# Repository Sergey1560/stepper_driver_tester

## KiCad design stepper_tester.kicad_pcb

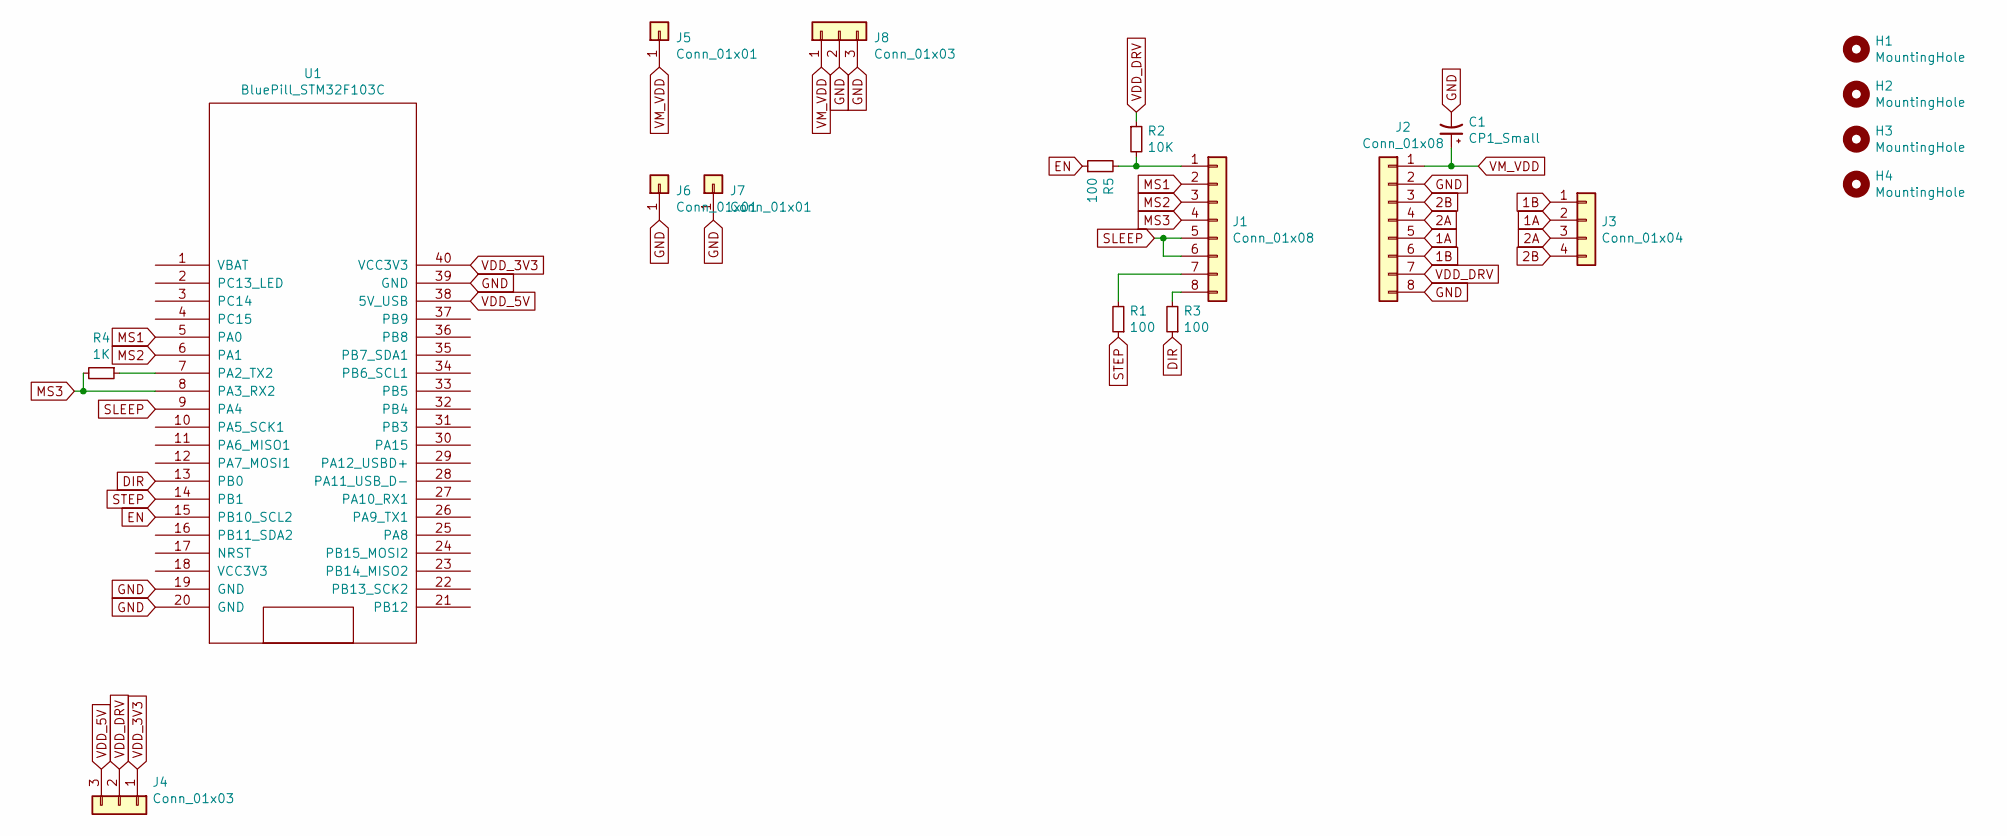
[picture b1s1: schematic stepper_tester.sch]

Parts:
C1: CP1_Small; CP_Radial_D8.0mm_P5.00mm
H1, H2, H3, H4: MountingHole; MountingHole_3.2mm_M3
J1, J2: Conn_01x08; PinSocket_1x08_P2.54mm_Vertical
J3: Conn_01x04; JST_XH_B4B-XH-A_1x04_P2.50mm_Vertical
J4: Conn_01x03; PinHeader_1x03_P2.54mm_Vertical
J5, J6, J7: Conn_01x01; PinHeader_1x01_P2.54mm_Vertical
J8: Conn_01x03; DC55x21THT
R1, R3, R5: 100; R_0805_2012Metric_Pad1.15x1.40mm_HandSolder
R2: 10K; R_0805_2012Metric_Pad1.15x1.40mm_HandSolder
R4: 1K; R_0805_2012Metric_Pad1.15x1.40mm_HandSolder
U1: BluePill_STM32F103C; ChinaBluePill

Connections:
1A: J2.5, J3.2
1B: J2.6, J3.1
2A: J2.4, J3.3
2B: J2.3, J3.4
DIR: R3.1, U1.13 (PB0)
EN: R5.1, U1.15 (PB10_SCL2)
GND: C1.2, J2.2, J2.8, J6.1, J7.1, J8.2, J8.3, U1.19 (GND), U1.20 (GND), U1.39 (GND)
MS1: J1.2, U1.5 (PA0)
MS2: J1.3, U1.6 (PA1)
MS3: J1.4, R4.2, U1.8 (PA3_RX2)
unnamed: J1.1, R2.2, R5.2
unnamed: J1.7, R1.2
unnamed: J1.8, R3.2
unnamed: R4.1, U1.7 (PA2_TX2)
SLEEP: J1.5, J1.6, U1.9 (PA4)
STEP: R1.1, U1.14 (PB1)
VDD_3V3: J4.1, U1.40 (VCC3V3)
VDD_5V: J4.3, U1.38 (5V_USB)
VDD_DRV: J2.7, J4.2, R2.1
VM_VDD: C1.1, J2.1, J5.1, J8.1

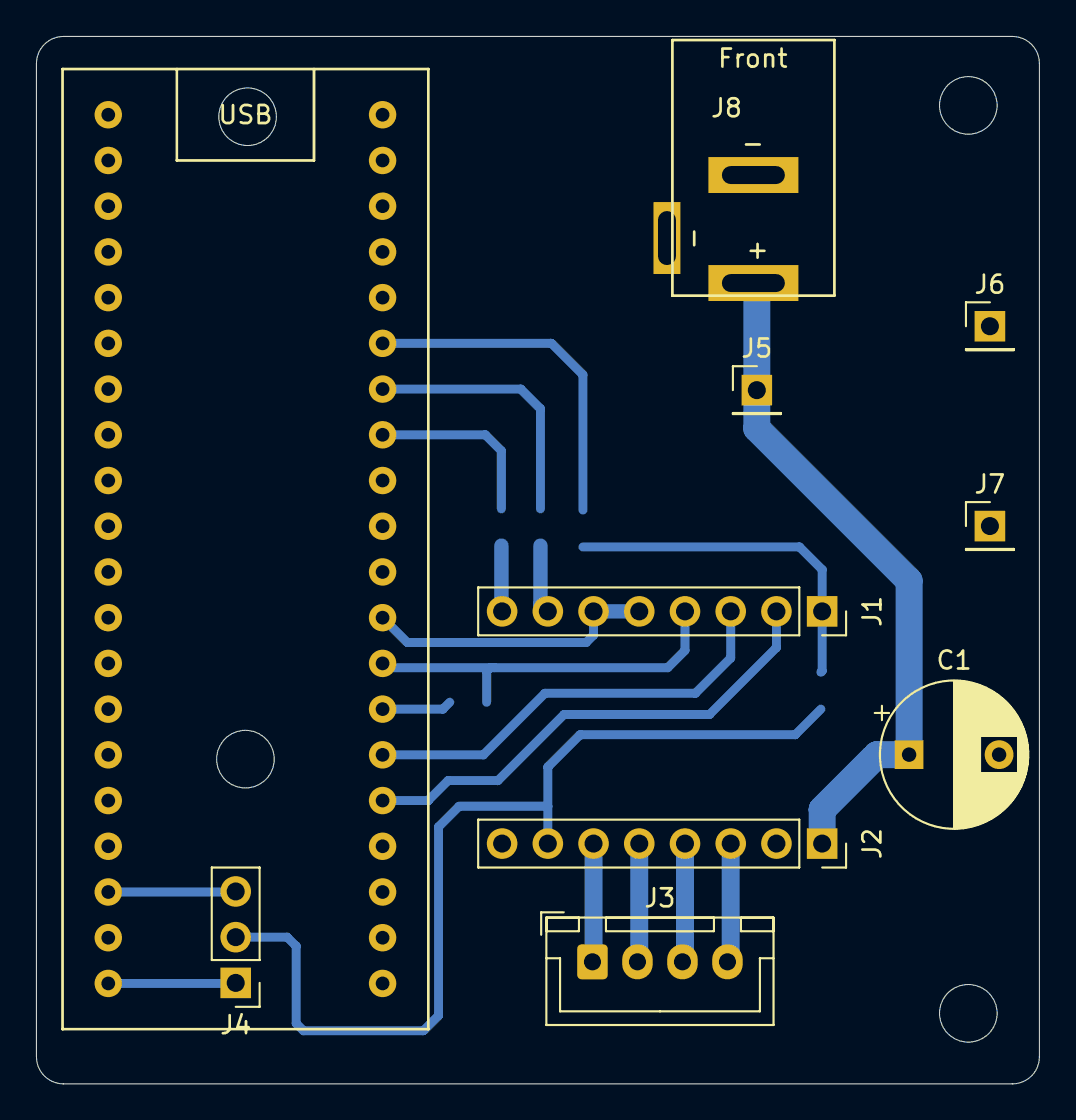
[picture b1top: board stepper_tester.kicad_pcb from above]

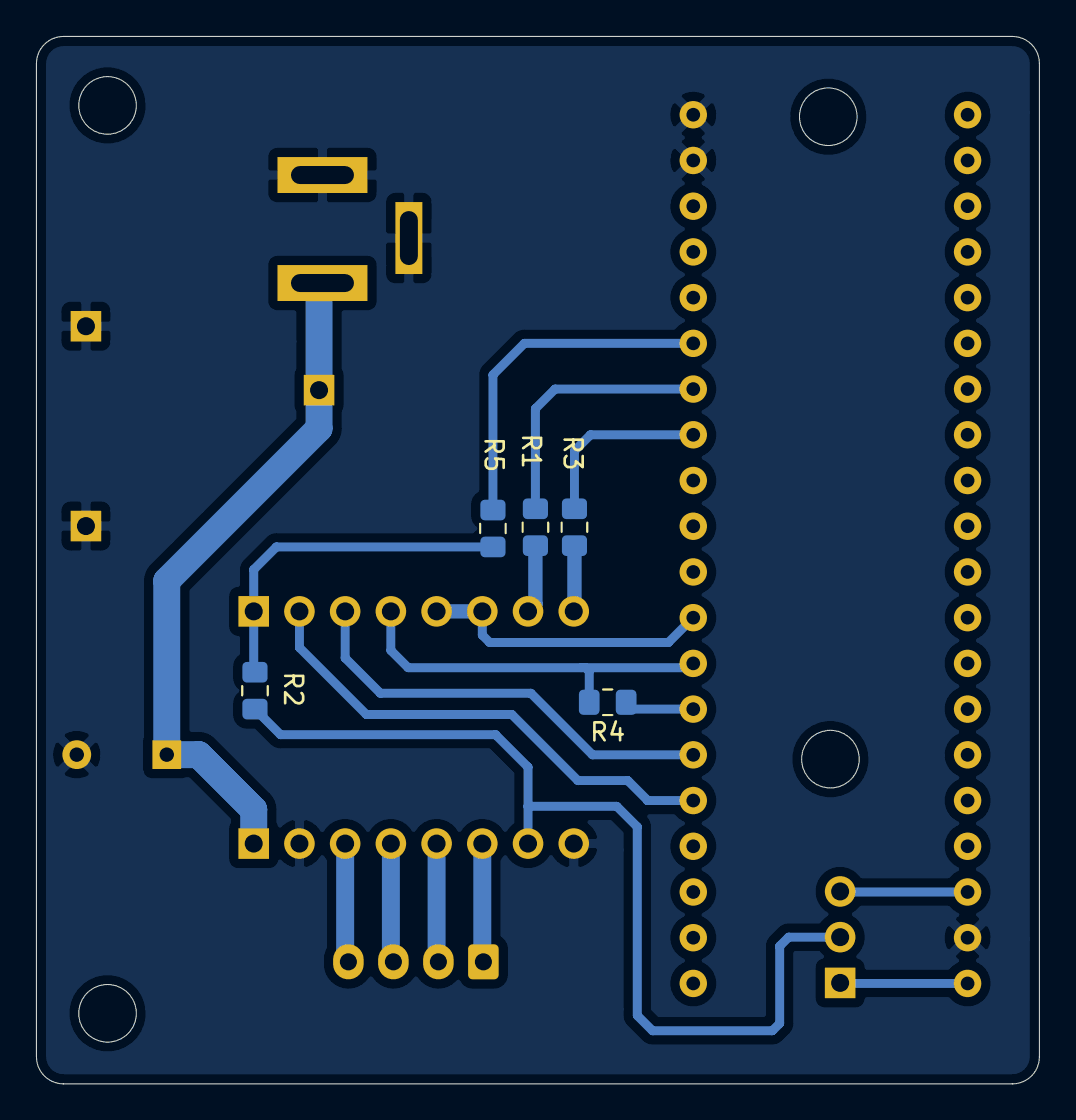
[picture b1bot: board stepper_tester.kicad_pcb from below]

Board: 2 copper layers, 55.7 x 58.2 mm, 19 parts (5 on the bottom side), 20 nets.

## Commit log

2020-11-13 Initial
2020-11-13 readme
2020-11-13 image url
2020-11-13 img url
2020-11-13 Power connector, 90 deg rotation
2020-11-17 Схема
